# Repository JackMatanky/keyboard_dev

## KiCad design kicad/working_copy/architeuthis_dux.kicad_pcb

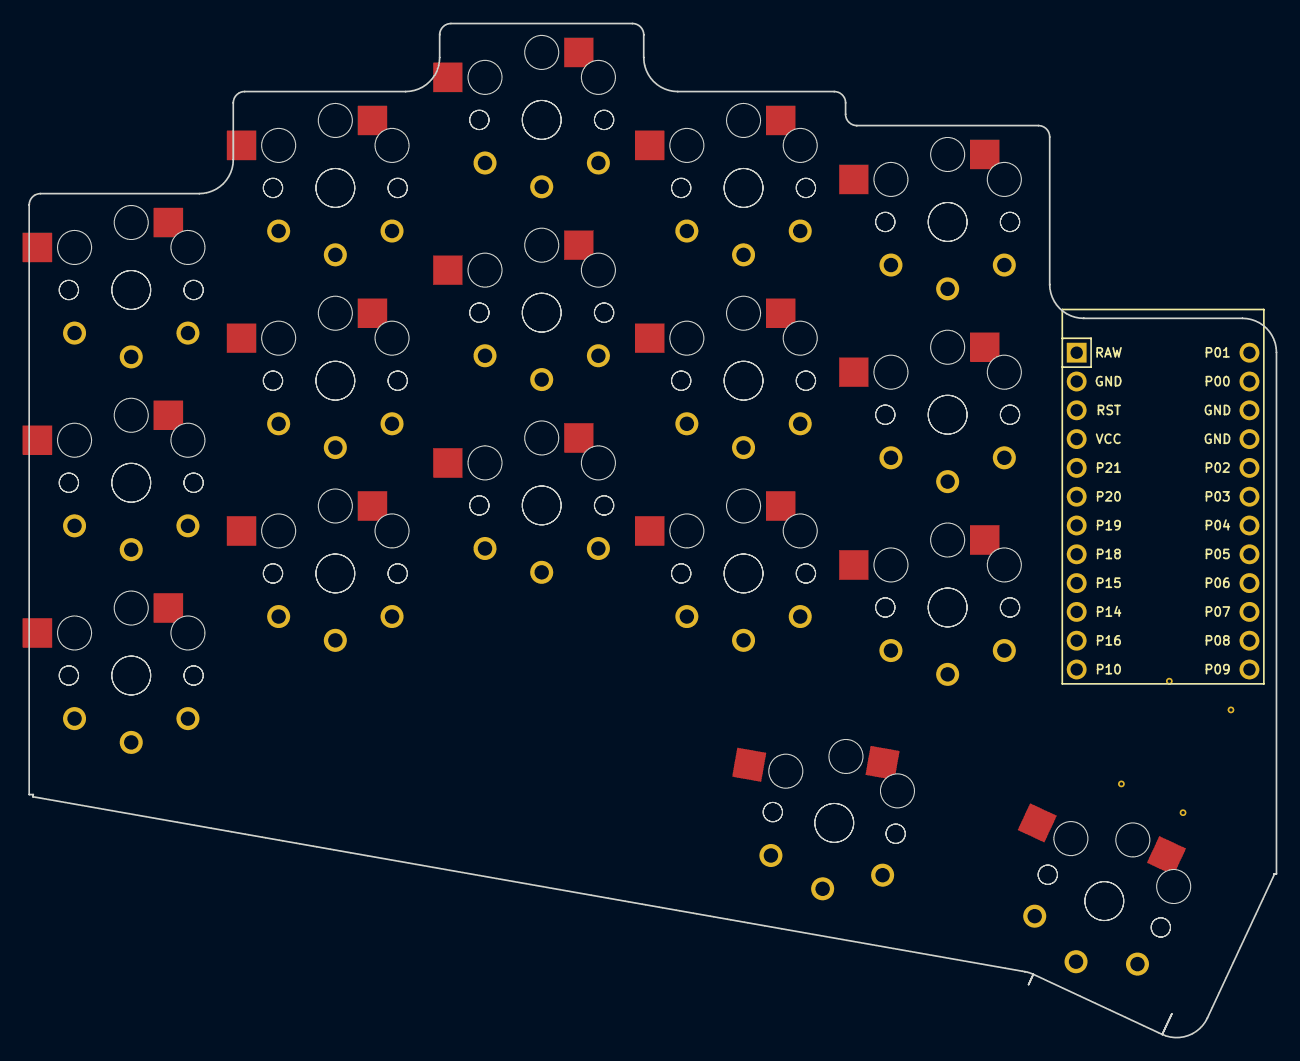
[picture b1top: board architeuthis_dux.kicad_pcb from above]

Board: 2 copper layers, 110.0 x 89.4 mm, 35 parts (0 on the bottom side), 18 nets, no tracks yet.

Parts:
MCU1: ProMicro
S1, S2, S3, S4, S5, S6, S7, S8, S9, S10, S11, S12, S13, S14, S15, S16, S17, S18, S19, S20, S21, S22, S23, S24, S25, S26, S27, S28, S29, S30, S31, S32, S33, S34: PG1350

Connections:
GND: MCU1.2, MCU1.15, MCU1.16, S1.2, S2.2, S3.2, S4.2, S5.2, S6.2, S7.2, S8.2, S9.2, S10.2, S11.2, S12.2, S13.2, S14.2, S15.2, S16.2, S17.2, S18.2, S19.2, S20.2, S21.2, S22.2, S23.2, S24.2, S25.2, S26.2, S27.2, S28.2, S29.2, S30.2, S31.2, S32.2, S33.2, S34.2
P0: MCU1.14, S11.1, S12.1
P1: MCU1.13, S13.1, S14.1
P3: MCU1.18, S9.1, S10.1
P4: MCU1.19, S7.1, S8.1
P5: MCU1.20, S5.1, S6.1
P6: MCU1.21, S3.1, S4.1
P7: MCU1.22, S1.1, S2.1
P8: MCU1.23, S31.1, S32.1
P9: MCU1.24, S33.1, S34.1
P10: MCU1.12, S25.1, S26.1
P14: MCU1.10, S21.1, S22.1
P15: MCU1.9, S19.1, S20.1
P16: MCU1.11, S23.1, S24.1
P18: MCU1.8, S17.1, S18.1
P19: MCU1.7, S15.1, S16.1
P20: MCU1.6, S27.1, S28.1
P21: MCU1.5, S29.1, S30.1

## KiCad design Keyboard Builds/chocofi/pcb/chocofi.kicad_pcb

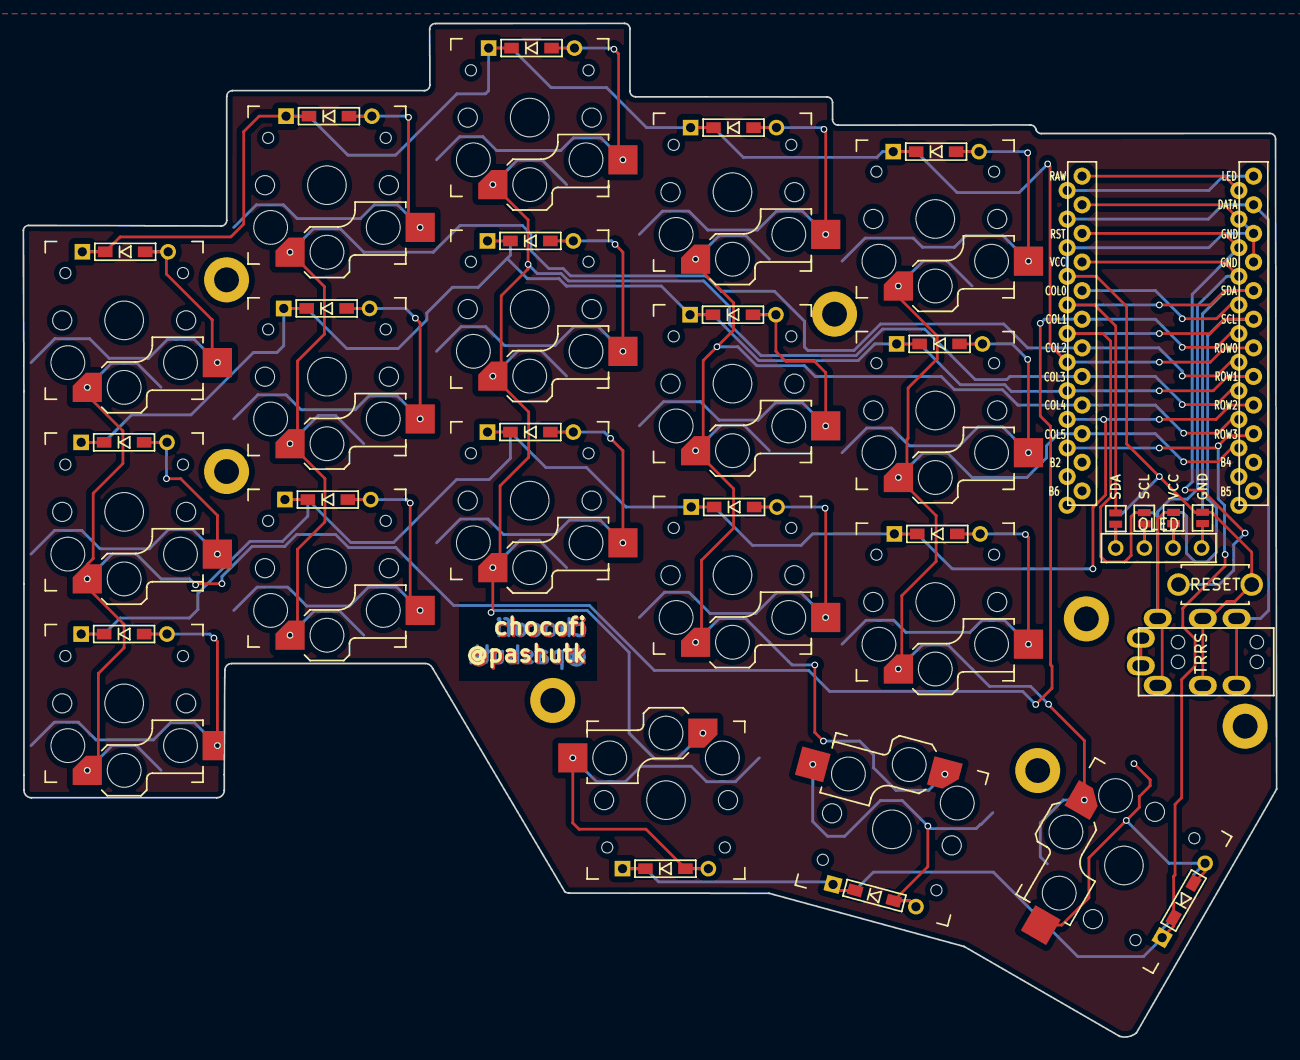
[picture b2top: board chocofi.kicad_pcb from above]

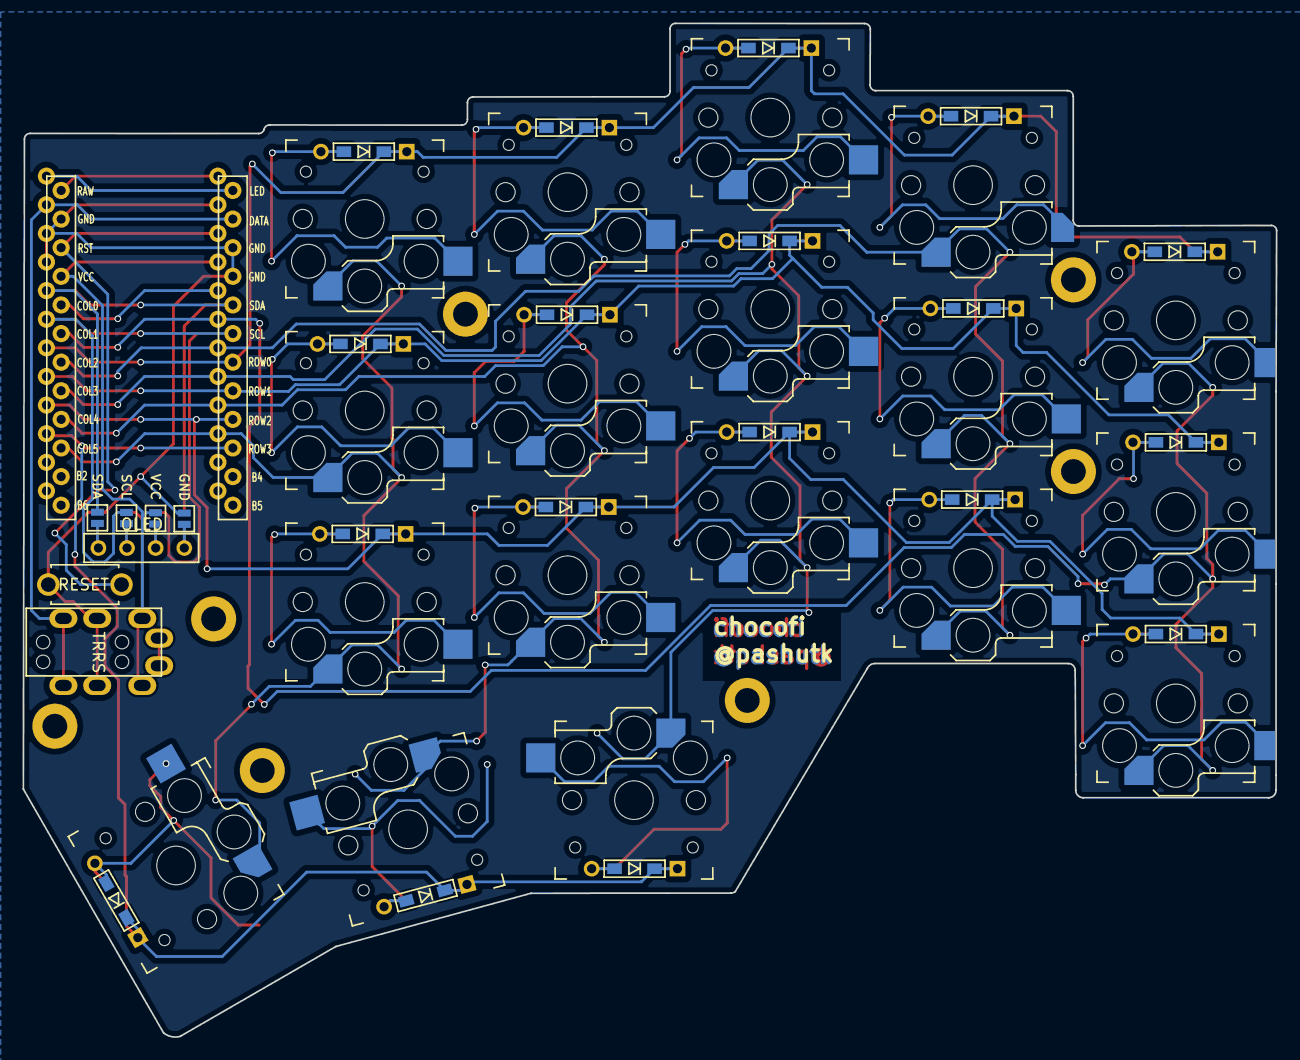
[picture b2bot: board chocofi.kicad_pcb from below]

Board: 2 copper layers, 111.3 x 90.0 mm, 55 parts (4 on the bottom side), 37 nets.

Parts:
D2, D3, D4, D5, D6, D8, D9, D10, D11, D12, D14, D15, D16, D17, D18, D19, D20, D21: D; D3_TH_SMD
H1: h1; LEGO_HOLE
J1: MJ-4PP-9
J2: OLED
JP6, JP61: SDA; Jumper
JP62, JP68: GND; Jumper
JP63, JP66: SCL; Jumper
JP64, JP65: VCC; Jumper
RSW1: Val**; ResetSW
SW2, SW3, SW4, SW5, SW6, SW8, SW9, SW10, SW11, SW12, SW14, SW15, SW16, SW17, SW18, SW19, SW20, SW21: SW_PUSH; Kailh_socket_PG1350_reversible
U1: ProMicro; ProMicro_v2
h2: h2; LEGO_HOLE
h3: h3; LEGO_HOLE
h4: h4; LEGO_HOLE
h5: h5; LEGO_HOLE
h6: h6; LEGO_HOLE
h7: h7; LEGO_HOLE

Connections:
GND: J1.C, JP62.1, JP68.1, RSW1.1, U1.3, U1.4, U1.23
unnamed: D2.2, SW2.2
unnamed: D3.2, SW3.2
unnamed: D4.2, SW4.2
unnamed: D5.2, SW5.2
unnamed: D6.2, SW6.2
unnamed: D8.2, SW8.2
unnamed: D9.2, SW9.2
unnamed: D10.2, SW10.2
unnamed: D11.2, SW11.2
unnamed: D12.2, SW12.2
unnamed: D14.2, SW14.2
unnamed: D15.2, SW15.2
unnamed: D16.2, SW16.2
unnamed: D17.2, SW17.2
unnamed: D18.2, SW18.2
unnamed: D19.2, SW19.2
unnamed: D20.2, SW20.2
unnamed: D21.2, SW21.2
unnamed: J2.3, JP65.2, JP66.2
unnamed: J2.4, JP6.2, JP68.2
unnamed: J2.2, JP63.2, JP64.2
unnamed: J2.1, JP61.2, JP62.2
SCL: JP63.1, JP66.1, U1.6
SDA: JP6.1, JP61.1, U1.5
VCC: J1.D, JP64.1, JP65.1, U1.21
col1: SW2.1, SW8.1, SW14.1, U1.19
col2: SW3.1, SW9.1, SW15.1, U1.18
col3: SW4.1, SW10.1, SW16.1, SW19.1, U1.17
col4: SW5.1, SW11.1, SW17.1, SW20.1, U1.16
col5: SW6.1, SW12.1, SW18.1, SW21.1, U1.15
data: J1.B, U1.2
reset: RSW1.2, U1.22
row0: D2.1, D3.1, D4.1, D5.1, D6.1, U1.7
row1: D8.1, D9.1, D10.1, D11.1, D12.1, U1.8
row2: D14.1, D15.1, D16.1, D17.1, D18.1, U1.9
row3: D19.1, D20.1, D21.1, U1.10

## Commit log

2022-11-11 commit -m
2023-01-03 add all existing files to keyboard dev repository
2023-01-03 update files
2023-01-10 commit after reorganizing files
2023-01-10 worked zmk shield
